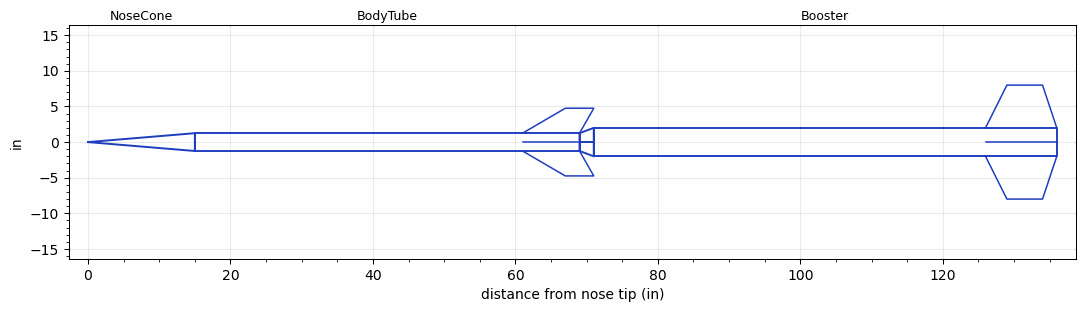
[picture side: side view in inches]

<RASAeroDocument>
 <FileVersion>2</FileVersion>
 <RocketDesign>
  <NoseCone>
   <Length>15</Length>
   <Diameter>2.5</Diameter>
   <Shape>Conical</Shape>
   <Location>0</Location>
  </NoseCone>
  <BodyTube>
   <Length>54</Length>
   <Diameter>2.5</Diameter>
   <Location>15</Location>
   <Fin>
    <Count>4</Count>
    <Chord>8</Chord>
    <Span>3.5</Span>
    <SweepDistance>6</SweepDistance>
    <TipChord>4</TipChord>
    <Thickness>0.187</Thickness>
    <LERadius>0.01</LERadius>
    <Location>8</Location>
    <AirfoilSection>Hexagonal</AirfoilSection>
    <FX1>0.5</FX1>
    <FX3>0.5</FX3>
   </Fin>
  </BodyTube>
  <Booster>
   <Length>65</Length>
   <Diameter>4</Diameter>
   <InsideDiameter>2.5</InsideDiameter>
   <Location>69</Location>
   <ShoulderLength>2</ShoulderLength>
   <Fin>
    <Count>4</Count>
    <Chord>10</Chord>
    <Span>6</Span>
    <SweepDistance>3</SweepDistance>
    <TipChord>5</TipChord>
    <Thickness>0.187</Thickness>
    <LERadius>0.01</LERadius>
    <Location>10</Location>
    <AirfoilSection>Hexagonal</AirfoilSection>
    <FX1>0.75</FX1>
    <FX3>0.75</FX3>
   </Fin>
  </Booster>
  <Surface>Camouflage Paint</Surface>
  <ModifiedBarrowman>True</ModifiedBarrowman>
  <Turbulence>True</Turbulence>
  <UseBooster1>False</UseBooster1>
  <UseBooster2>False</UseBooster2>
 </RocketDesign>
 <LaunchSite>
  <Altitude>3700</Altitude>
  <Pressure>29.92</Pressure>
  <RodAngle>1</RodAngle>
  <RodLength>20</RodLength>
  <Temperature>80</Temperature>
  <WindSpeed>5</WindSpeed>
 </LaunchSite>
 <Recovery>
  <Altitude1>1000</Altitude1>
  <Altitude2>1000</Altitude2>
  <DeviceType1>None</DeviceType1>
  <DeviceType2>None</DeviceType2>
  <Event1>False</Event1>
  <Event2>False</Event2>
  <Size1>1</Size1>
  <Size2>1</Size2>
  <EventType1>None</EventType1>
  <EventType2>None</EventType2>
  <CD1>1.33</CD1>
  <CD2>1.33</CD2>
 </Recovery>
 <SimulationList>
  <Simulation>
   <SustainerEngine>M2773  (TsKrush)</SustainerEngine>
   <SustainerLaunchWt>16.2</SustainerLaunchWt>
   <SustainerCG>44.04</SustainerCG>
   <SustainerIgnitionDelay>10</SustainerIgnitionDelay>
   <Booster1Engine>O6096  (TsKrush)</Booster1Engine>
   <Booster1LaunchWt>51.3</Booster1LaunchWt>
   <Booster1SeparationDelay>0</Booster1SeparationDelay>
   <Booster1IgnitionDelay>0</Booster1IgnitionDelay>
   <Booster1CG>87.05</Booster1CG>
   <IncludeBooster1>True</IncludeBooster1>
   <Booster2Delay>0</Booster2Delay>
   <IncludeBooster2>False</IncludeBooster2>
   <TimetoApogee>176.3945</TimetoApogee>
   <MaxAltitude>455545.8</MaxAltitude>
   <MaxVelocity>6068.397</MaxVelocity>
  </Simulation>
 </SimulationList>
</RASAeroDocument>
